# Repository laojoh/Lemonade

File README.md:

# Lemonade

An open source, pocket-sized game console, able to load any pygame program with just a little modification! Parts are relatively cheap, and it's **open source**, meaning anyone can make it (with enough movitvation)! 

## Use

**THIS BRANCH IS THE DESKTOP VERSION. PLEASE SWITCH BRANCHES TO "console" FOR THE CONSOLE VERSION IN THE EVENT YOU ARE BUILDING IT**

Check out the **console** onshape link!

https://cad.onshape.com/documents/b190164d285ac74417b1d1a8/w/ccaa6db00e3677430904407c/e/88483beccc87a88b48fd7f32

### Installation

To be completely honest, this branch is just to test code and logic before going into the tft display, but I got the idea to make a desktop version!

To install, simply clone this repo and run the Home.py file, and kaboom! Running Lemonade OS. 

## Making your own GAME :O

If you want to make your OWN PERSONAL CUSTOM GAME (or have a folder of one already), follow these steps to ensure you encounter the least amount of roadblocks to get it up and running.

### 1. Install VSCode

It's a nice IDE to have and works well when editing things

### 2. Access the assets folder inside Lemonade

This is where each individual game is.

### 3. Move (or copypaste) your game folder into the assets folder

Make sure your game class has a run function, and be sure that it doesn't call it at the end of the game file!

### 4. Modifying Home.py

Inside Home.py, at the top, you'll see many many imports. 
Add an import to your game. It should look something like

```
from [game folder].[game file] import [game class]
```

Then, go down to somewhere around line 55. Notice how this is where all the games executions happen. Since there are only 4 slots, choose one game to replace. Game1 is the Ninja Platformer, Game2 is Snake Game, Game3 is Sudoku, and Game4 is Tetris. Replace one of the ```Game[number]().run()``` with your own ```[your game class]().run()```

Then, boot up Home.py and switch to the tile your game replaced (using arrow keys) and hit x to launch.

Tada!! You have now added your own game to Lemonade :)

## Why?
You might be asking yourself, why make this in the first place??

Well, here's your answer. Cheapish game consoles don't really exist anymore. the 3DS and gameboy aren't really around (albeit people still have them), and the nintendo switch or steamdeck is just wayyy too much, not only in terms of price, but also in size. The Playdate is the size exception, but not the price exception. Making this an open source project allows people to make their own games, learn pygame, and be able to use it for entertainment!

Lemonade in essence extends opportunity in python coding to people who may not have much experience, especially in the desktop version! It is able to act as a medium for people to share and make games and play them. 

## Images

.png)

.png)

.png)

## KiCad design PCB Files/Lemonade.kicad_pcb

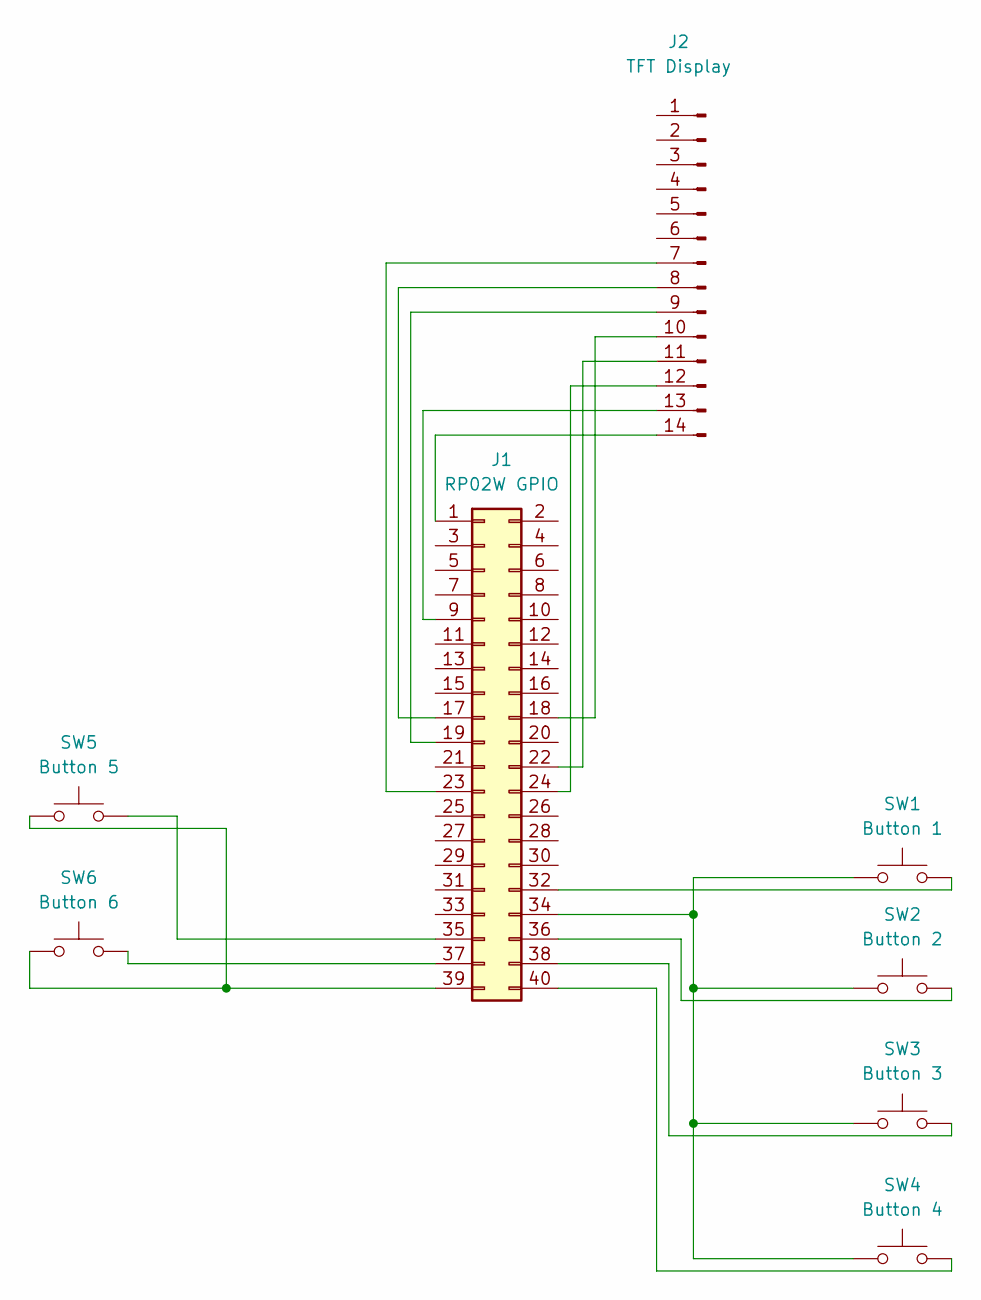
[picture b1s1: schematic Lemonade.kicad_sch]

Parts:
J1: RP02W GPIO; PinHeader_2x20_P2.54mm_Vertical
J2: TFT Display; PinHeader_1x14_P2.54mm_Vertical
SW1: Button 1; SW_TH_Tactile_Omron_B3F-102x
SW2: Button 2; SW_TH_Tactile_Omron_B3F-102x
SW3: Button 3; SW_TH_Tactile_Omron_B3F-102x
SW4: Button 4; SW_TH_Tactile_Omron_B3F-102x
SW5: Button 5; SW_TH_Tactile_Omron_B3F-102x
SW6: Button 6; SW_TH_Tactile_Omron_B3F-102x

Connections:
unnamed: J1.1, J2.14
unnamed: J1.9, J2.13
unnamed: J1.17, J2.8
unnamed: J1.18, J2.10
unnamed: J1.19, J2.9
unnamed: J1.22, J2.11
unnamed: J1.23, J2.7
unnamed: J1.24, J2.12
unnamed: J1.32, SW1.2
unnamed: J1.34, SW1.1, SW2.1, SW3.1, SW4.1
unnamed: J1.35, SW5.2
unnamed: J1.36, SW2.2
unnamed: J1.37, SW6.2
unnamed: J1.38, SW3.2
unnamed: J1.39, SW5.1, SW6.1
unnamed: J1.40, SW4.2

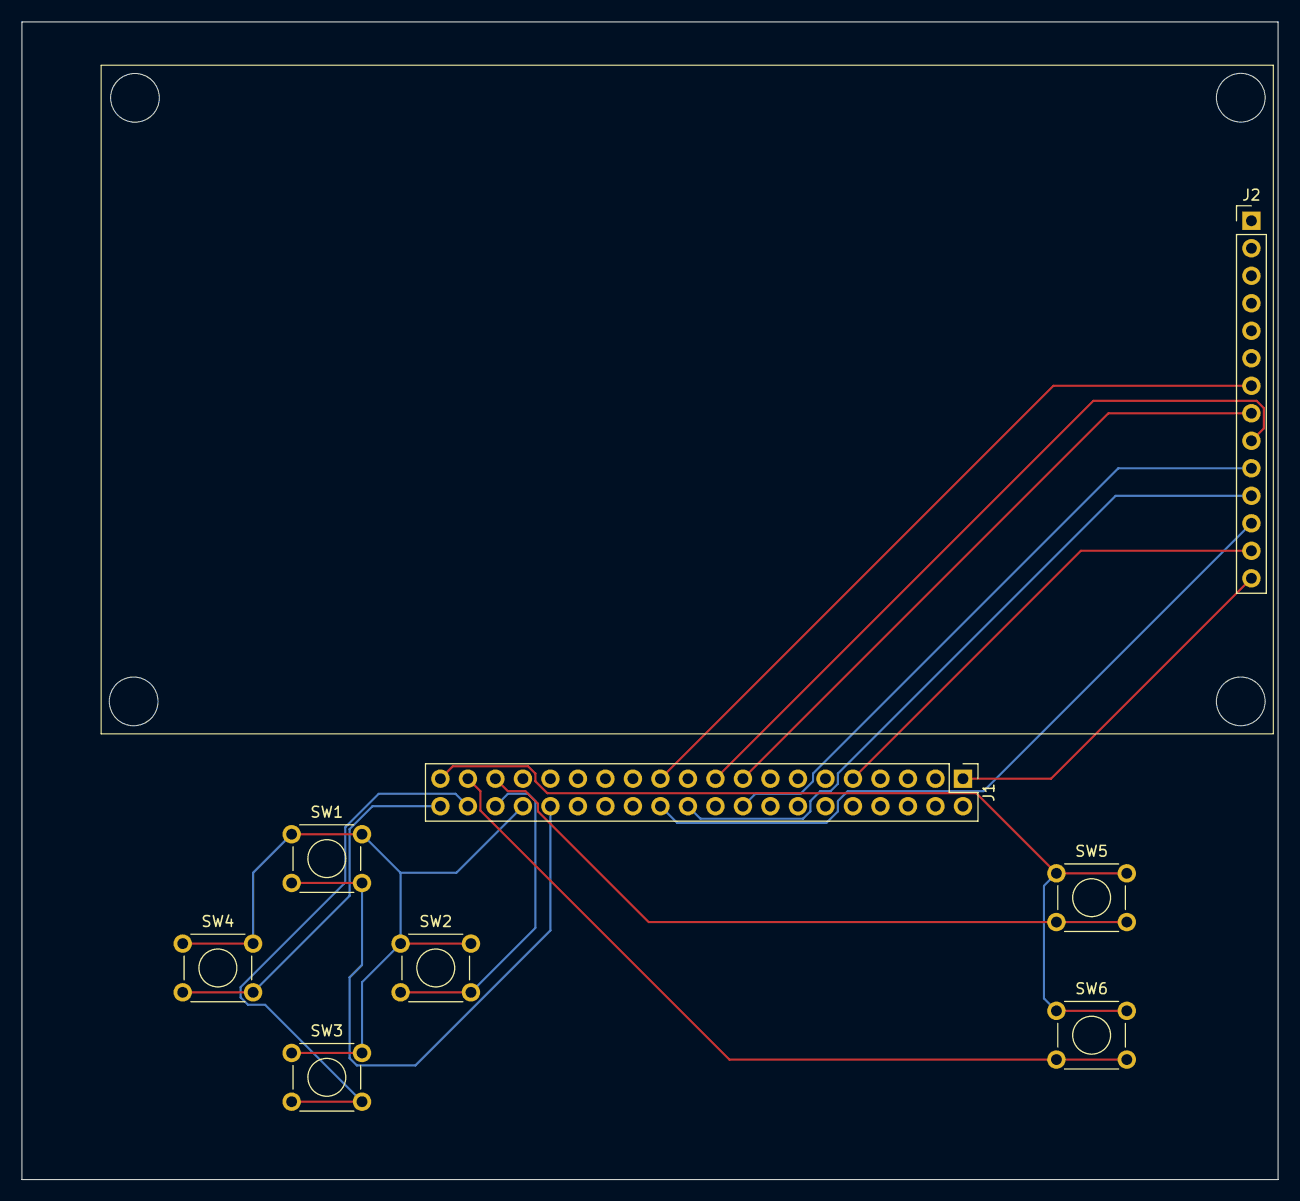
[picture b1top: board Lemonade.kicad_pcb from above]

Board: 2 copper layers, 116.0 x 106.9 mm, 8 parts (0 on the bottom side), 16 nets.

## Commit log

2026-04-23 rename
2026-06-06 big ahh commit for game progress - testing if works on putty
2026-06-08 configred Game.py for framebuffer output, changed editor screen size to match game display size and writing directly to /dev/fb0
2026-06-08 uhh reverted back to desktop vers
2026-06-08 console game.py
2026-06-08 did some more work on console - save before reboot
2026-06-08 IT DISPLAYS ON THE TFT DISPLAY WOOOOOOOOOO
2026-06-13 More game progress, added dashing and wall sliding also limited jumps and particles!
2026-06-14 Syncing code progress from main ---> console
2026-06-15 Game #1 (Ninja Platformer) FINISHED! Created 2 more levels
2026-06-15 Got the console branch caught up, but still trying to figure out screenshake
2026-06-15 Hopeful scr
2026-06-15 update readme yet again
2026-06-16 check if works on screen now
2026-06-16 check 2
2026-06-16 check 3
2026-06-16 YAY IT DISPLAYS but tiles are
2026-06-16 check 4
2026-06-16 check 5
2026-06-16 check 6
2026-06-16 check 7
2026-06-16 check 8
2026-06-16 check 9
2026-06-16 check 10
2026-06-16 check 11
2026-06-16 check 12
2026-06-16 check 13
2026-06-16 check 14
2026-06-16 check 15
2026-06-16 check 16
2026-06-16 I give up on weird tft colors
2026-06-16 one moreee tiemeee
2026-06-16 aw hell naw
2026-06-16 check 17
2026-06-16 check 18
2026-06-16 check 19
2026-06-16 console
2026-06-16 check big 2 0
2026-06-16 check 21
2026-06-16 chillout
2026-06-16 check 22
2026-06-16 give up for now
2026-06-16 gpio test 1
2026-06-16 gpio test 2
2026-06-16 gpio test 3
2026-06-16 gpio test 4
2026-06-16 gpio test 5
2026-06-16 oh my god the buttons work
2026-06-16 fixing jumping mechanics
2026-06-16 2nd fix for jump
2026-06-16 oops
2026-06-16 more fixy fixy
2026-06-16 oopsies pt.2
2026-06-16 forgor to fix wallslide jump
2026-06-16 tile fix????? pls
2026-06-16 uhh idk why these change so much
2026-06-16 tile fix pt.2 maybe perchance mayhaps
2026-06-16 tile fix PLEASE
2026-06-16 TILE PLEASE FIX
2026-06-16 pls tiles
2026-06-16 i don't know what's going on
2026-06-16 if +1 doesn't work, -8 might?
2026-06-16 that didn't work now I'm more than confused
2026-06-16 I'm going to explode
2026-06-17 tile fix maybe
2026-06-17 fixed tiles! now onto performance checking
2026-06-17 oopsz
2026-06-17 testing instant
2026-06-17 test test 123 seeing if pygame2.6 works on rp
2026-06-17 tobytes doesn't work D:
2026-06-17 wawawa
2026-06-17 pls fix speed
2026-06-17 performance fix trial
2026-06-17 testing color yet again
2026-06-17 testing whether transform is the color culprit
2026-06-17 testing whether its the conversion or something else
2026-06-17 testing convert i think?
2026-06-17 testing with a bmp
2026-06-17 oopz
2026-06-17 weeeee
2026-06-17 still trying to test bmp
2026-06-17 forgot to take out green fill
2026-06-17 trial 2 for color correcting
2026-06-17 checking pixel differences
2026-06-17 pixel diff 2
2026-06-17 testing stark contrast
2026-06-17 it's a not quite true colors issue - not bright enough?
2026-06-17 not quite there, better though
2026-06-17 more home menu
2026-06-17 fix for pathfinding in rc.local
2026-06-17 oops nvm
2026-06-17 now I'm confused
2026-06-17 finally got the home page game running part to work
2026-06-18 Rename fallout_zine_template.pdf to Lemonade_Zine_pdf
2026-06-18 more work on home page
2026-06-18 Add image link for Fallout zine page in README
    Added an image link to the README for visual reference.
2026-06-18 added png to display on readme
2026-06-18 reordering for console ui
2026-06-18 oopsi
2026-06-18 uhhh?
2026-06-18 updating path for raspbian
2026-06-18 fix2
2026-06-18 fix3
2026-06-18 test??
2026-06-18 test 2
2026-06-18 more test
2026-06-18 testy aaa
2026-06-18 retest
2026-06-18 testyman
2026-06-18 testing homepage fb
2026-06-18 fixed transform err
2026-06-18 fixed error again
2026-06-18 color fix?
2026-06-18 more color fix
2026-06-18 more colortesting
2026-06-18 yet another color
2026-06-18 commma.
2026-06-18 color testing
2026-06-18 color test lets just say number 8
2026-06-18 color 9
2026-06-18 color 10
2026-06-18 color11
2026-06-18 buttons check
2026-06-18 btn ch
2026-06-18 gamer test
2026-06-18 testing
2026-06-18 forgot something
2026-06-18 I have to do this every time man
2026-06-18 fixed pathfinding?
2026-06-18 paths omg
2026-06-18 fixing title readability
2026-06-18 colorgot cooked, maybe bolding?
2026-06-18 testing game integration
2026-06-18 game launch fix?
2026-06-18 game launch fix.
2026-06-18 game launch fix fix
2026-06-18 preventing multiple button assignments to a single gpio pin
2026-06-18 another fix to gpio err
2026-06-18 for some reason these pyc files keep updating
2026-06-19 updating readme to make clear what branch is what
2026-06-19 added text and changed window sizes for desktop version
2026-06-20 got banner images to work!
2026-06-20 banner img test
2026-06-20 ooopz
2026-06-20 rerouting image paths
2026-06-20 adding a file
2026-06-20 uploading necessary imgs
2026-06-20 Add images to README for assembly and PCB
    Added images to the README for better visualization.
2026-06-20 renaming files and removing unnecessary code
2026-06-20 organizing
2026-06-20 Fix image paths in README.md
    Updated image paths in README.md to reflect new directory structure.
2026-06-20 Expand README with console usage instructions
    Added console setup instructions for Raspberry Pi, including cloning the repository and editing rc.local for driver execution on startup.
2026-06-21 Tetris!
2026-06-21 Tetrisss (pre configuration progress save)
2026-06-21 config for console?
2026-06-21 config 2
2026-06-21 config 3
2026-06-21 config 4
2026-06-21 config 5
2026-06-21 config 6
2026-06-21 testing bounce time
2026-06-21 forgot ms
2026-06-21 debounce
2026-06-21 colorz
2026-06-21 tuning debounce
2026-06-21 testing home button
2026-06-21 forgor de comma
2026-06-21 testing button inheritance
2026-06-21 testing bounce times?
2026-06-21 testing more button thingies
2026-06-21 interfacing game4 with home
2026-06-21 fixing homepage
2026-06-21 adding banners for homepage
2026-06-21 Modify startup script for Raspberry Pi
    Updated startup script instructions in README.
2026-06-21 repo things
2026-06-21 forgot banner!
2026-06-21 Update BOM with new URLs and prices
    Updated links for components and corrected pricing.
